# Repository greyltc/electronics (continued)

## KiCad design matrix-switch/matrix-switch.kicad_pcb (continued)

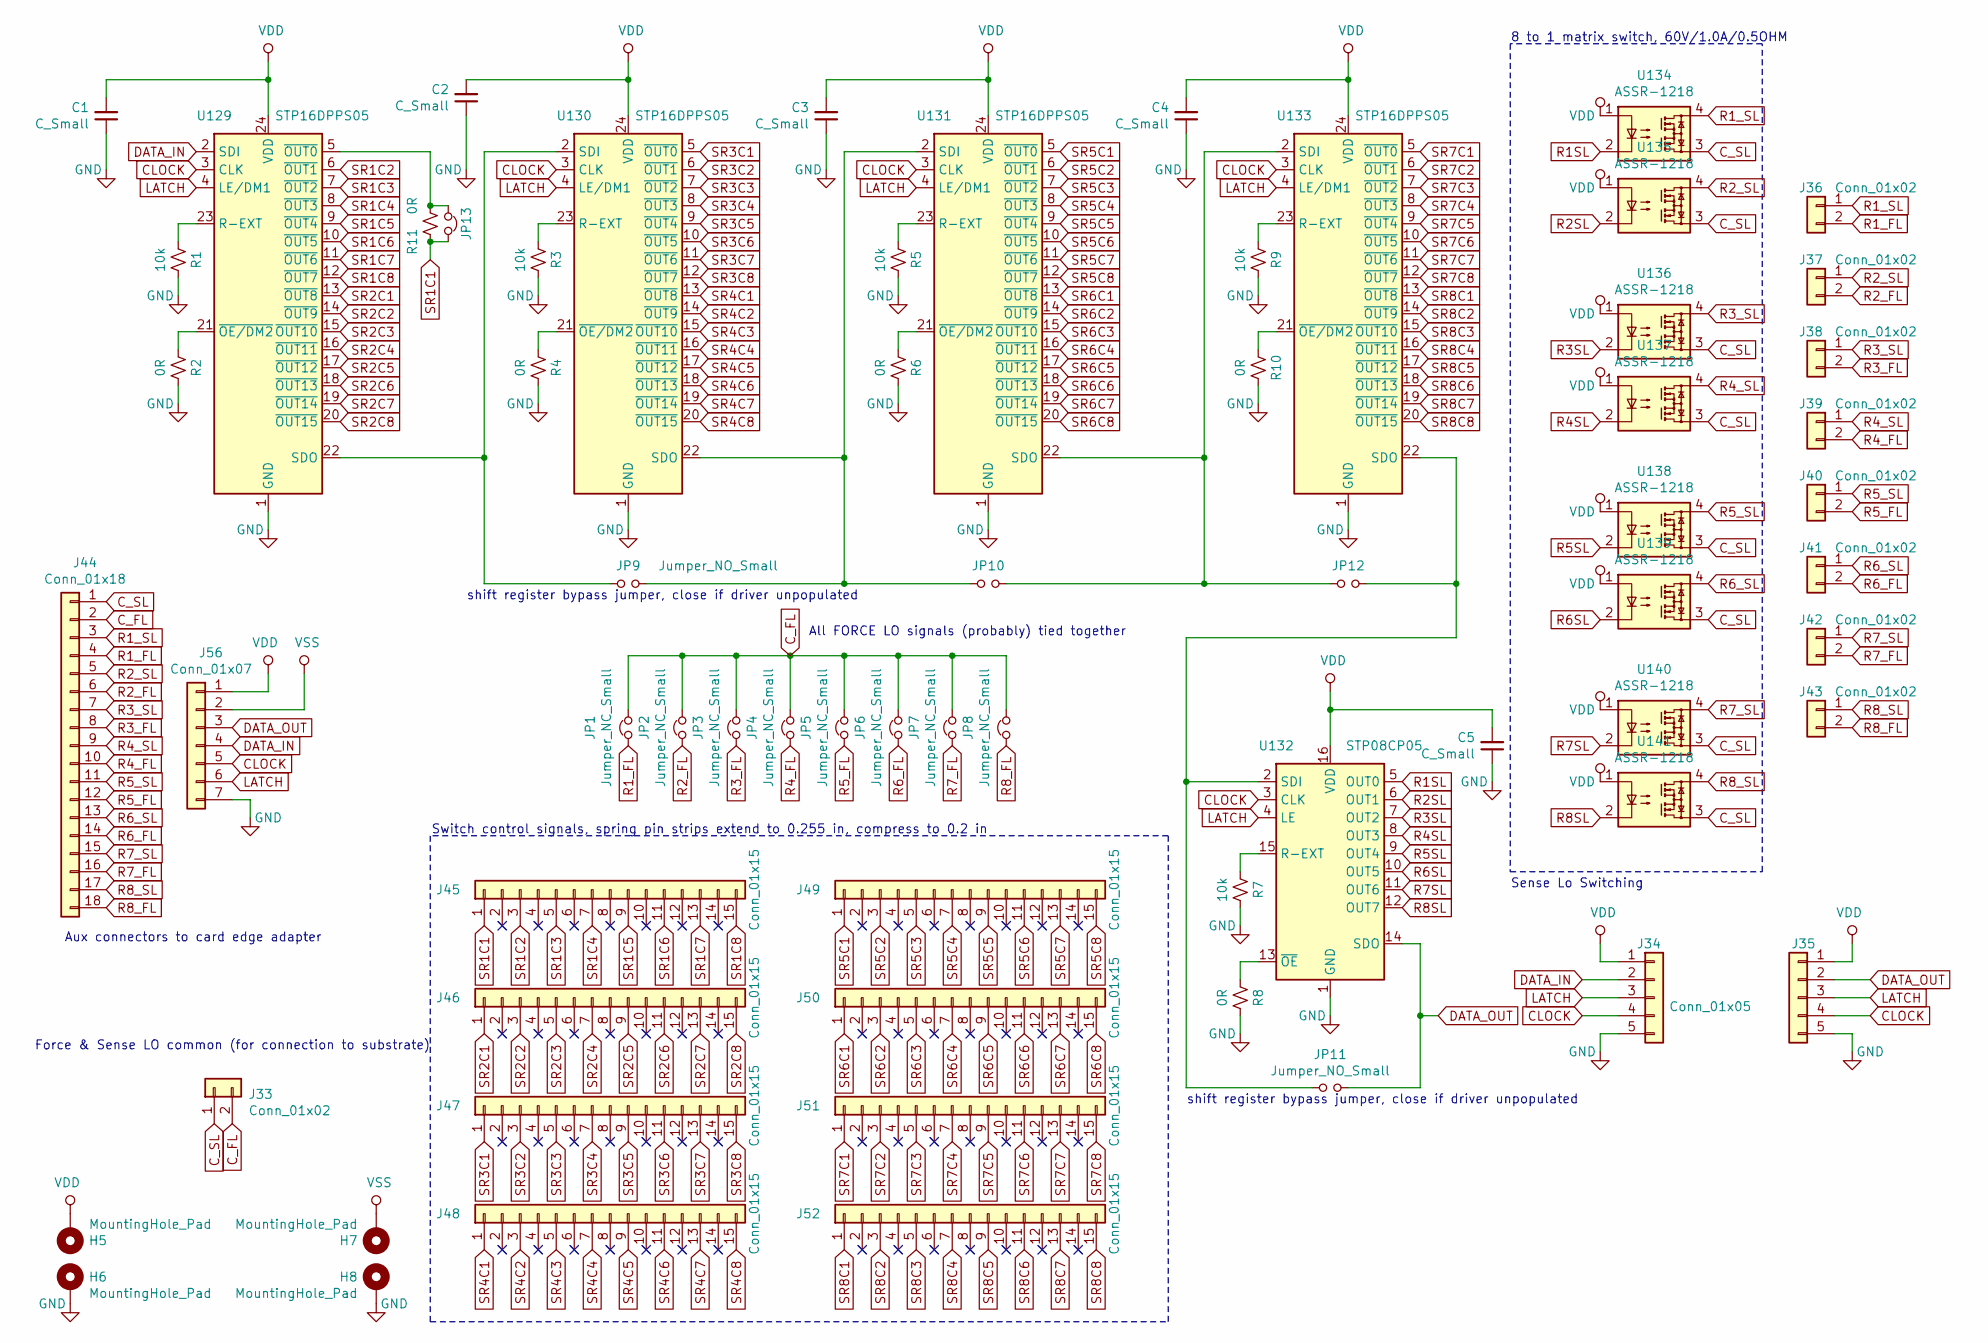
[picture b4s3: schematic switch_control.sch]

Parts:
C1, C2, C3, C4, C5: C_Small; C_0805_2012Metric
H5, H6, H7, H8: MountingHole_Pad; MountingHole_2.2mm_M2_Pad_Via
J33, J36, J37, J38, J39, J40, J41, J42, J43: Conn_01x02; PinHeader_1x02_P2.54mm_Vertical
J34, J35: Conn_01x05; PinHeader_1x05_P2.54mm_Vertical
J44: Conn_01x18; PinHeader_1x18_P2.54mm_Vertical
J45, J46, J47, J48, J49, J50, J51, J52: Conn_01x15; PinHeader_1x15_P2.54mm_Vertical; mfg_part 812-22-064-30-000101 millmax
J56: Conn_01x07; PinHeader_1x07_P2.54mm_Vertical
JP1, JP2, JP3, JP4, JP5, JP6, JP7, JP8, JP13: Jumper_NC_Small; SolderJumper-2_P1.3mm_Bridged_RoundedPad1.0x1.5mm
JP9, JP10, JP11, JP12: Jumper_NO_Small; SolderJumper-2_P1.3mm_Open_RoundedPad1.0x1.5mm
R1, R3, R5, R7, R9: 10k; R_0805_2012Metric
R2, R4, R6, R8, R10, R11: 0R; R_0805_2012Metric
U129, U130, U131, U133: STP16DPPS05; SOIC-24W_7.5x15.4mm_P1.27mm
U132: STP08CP05; SOIC-16_3.9x9.9mm_P1.27mm
U134, U135, U136, U137, U138, U139, U140, U141: ASSR-1218; SO-4_4.4x4.3mm_P2.54mm

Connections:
CLOCK: J34.4, J35.4, J56.5, U129.3 (CLK), U130.3 (CLK), U131.3 (CLK), U132.3 (CLK), U133.3 (CLK); also elsewhere on the board
C_FL: J33.2, J44.2, JP1.2, JP2.2, JP3.2, JP4.2, JP5.2, JP6.2, JP7.2, JP8.2; also elsewhere on the board
C_SL: J33.1, J44.1, U134.3, U135.3, U136.3, U137.3, U138.3, U139.3, U140.3, U141.3; also elsewhere on the board
DATA_IN: J34.2, J56.4, U129.2 (SDI); also elsewhere on the board
DATA_OUT: J35.2, J56.3, JP11.2, U132.14 (SDO); also elsewhere on the board
GND: C1.1, C2.1, C3.1, C4.1, C5.1, H6.1, H8.1, J34.5, J35.5, J56.7, R1.1, R2.1, R3.1, R4.1, R5.1, R6.1, R7.1, R8.1, R9.1, R10.1, U129.1 (GND), U130.1 (GND), U131.1 (GND), U132.1 (GND), U133.1 (GND); also elsewhere on the board
LATCH: J34.3, J35.3, J56.6, U129.4 (LE/DM1), U130.4 (LE/DM1), U131.4 (LE/DM1), U132.4 (LE), U133.4 (LE/DM1); also elsewhere on the board
unnamed: JP9.1, U129.22 (SDO), U130.2 (SDI)
unnamed: JP9.2, JP10.1, U130.22 (SDO), U131.2 (SDI)
unnamed: JP10.2, JP12.1, U131.22 (SDO), U133.2 (SDI)
unnamed: JP11.1, JP12.2, U132.2 (SDI), U133.22 (SDO)
unnamed: JP13.1, R11.1, U129.5 (~OUT0)
unnamed: R1.2, U129.23 (R-EXT)
unnamed: R2.2, U129.21 (~OE/DM2)
unnamed: R3.2, U130.23 (R-EXT)
unnamed: R4.2, U130.21 (~OE/DM2)
unnamed: R5.2, U131.23 (R-EXT)
unnamed: R6.2, U131.21 (~OE/DM2)
unnamed: R7.2, U132.15 (R-EXT)
unnamed: R8.2, U132.13 (~OE)
unnamed: R9.2, U133.23 (R-EXT)
unnamed: R10.2, U133.21 (~OE/DM2)
R1SL: U132.5 (OUT0), U134.2
R1_FL: J36.2, J44.4, JP1.1; also elsewhere on the board
R1_SL: J36.1, J44.3, U134.4; also elsewhere on the board
R2SL: U132.6 (OUT1), U135.2
R2_FL: J37.2, J44.6, JP2.1; also elsewhere on the board
R2_SL: J37.1, J44.5, U135.4; also elsewhere on the board
R3SL: U132.7 (OUT2), U136.2
R3_FL: J38.2, J44.8, JP3.1; also elsewhere on the board
R3_SL: J38.1, J44.7, U136.4; also elsewhere on the board
R4SL: U132.8 (OUT3), U137.2
R4_FL: J39.2, J44.10, JP4.1; also elsewhere on the board
R4_SL: J39.1, J44.9, U137.4; also elsewhere on the board
R5SL: U132.9 (OUT4), U138.2
R5_FL: J40.2, J44.12, JP5.1; also elsewhere on the board
R5_SL: J40.1, J44.11, U138.4; also elsewhere on the board
R6SL: U132.10 (OUT5), U139.2
R6_FL: J41.2, J44.14, JP6.1; also elsewhere on the board
R6_SL: J41.1, J44.13, U139.4; also elsewhere on the board
R7SL: U132.11 (OUT6), U140.2
R7_FL: J42.2, J44.16, JP7.1; also elsewhere on the board
R7_SL: J42.1, J44.15, U140.4; also elsewhere on the board
R8SL: U132.12 (OUT7), U141.2
R8_FL: J43.2, J44.18, JP8.1; also elsewhere on the board
R8_SL: J43.1, J44.17, U141.4; also elsewhere on the board
SR1C1: J45.1, JP13.2, R11.2
SR1C2: J45.3, U129.6 (~OUT1)
SR1C3: J45.5, U129.7 (~OUT2)
SR1C4: J45.7, U129.8 (~OUT3)
SR1C5: J45.9, U129.9 (~OUT4)
SR1C6: J45.11, U129.10 (~OUT5)
SR1C7: J45.13, U129.11 (~OUT6)
SR1C8: J45.15, U129.12 (~OUT7)
SR2C1: J46.1, U129.13 (~OUT8)
SR2C2: J46.3, U129.14 (~OUT9)
SR2C3: J46.5, U129.15 (~OUT10)
SR2C4: J46.7, U129.16 (~OUT11)
SR2C5: J46.9, U129.17 (~OUT12)
SR2C6: J46.11, U129.18 (~OUT13)
SR2C7: J46.13, U129.19 (~OUT14)
SR2C8: J46.15, U129.20 (~OUT15)
SR3C1: J47.1, U130.5 (~OUT0)
SR3C2: J47.3, U130.6 (~OUT1)
SR3C3: J47.5, U130.7 (~OUT2)
SR3C4: J47.7, U130.8 (~OUT3)
SR3C5: J47.9, U130.9 (~OUT4)
SR3C6: J47.11, U130.10 (~OUT5)
SR3C7: J47.13, U130.11 (~OUT6)
SR3C8: J47.15, U130.12 (~OUT7)
SR4C1: J48.1, U130.13 (~OUT8)
SR4C2: J48.3, U130.14 (~OUT9)
SR4C3: J48.5, U130.15 (~OUT10)
SR4C4: J48.7, U130.16 (~OUT11)
SR4C5: J48.9, U130.17 (~OUT12)
SR4C6: J48.11, U130.18 (~OUT13)
SR4C7: J48.13, U130.19 (~OUT14)
SR4C8: J48.15, U130.20 (~OUT15)
SR5C1: J49.1, U131.5 (~OUT0)
SR5C2: J49.3, U131.6 (~OUT1)
SR5C3: J49.5, U131.7 (~OUT2)
SR5C4: J49.7, U131.8 (~OUT3)
SR5C5: J49.9, U131.9 (~OUT4)
SR5C6: J49.11, U131.10 (~OUT5)
SR5C7: J49.13, U131.11 (~OUT6)
SR5C8: J49.15, U131.12 (~OUT7)
SR6C1: J50.1, U131.13 (~OUT8)
SR6C2: J50.3, U131.14 (~OUT9)
SR6C3: J50.5, U131.15 (~OUT10)
SR6C4: J50.7, U131.16 (~OUT11)
SR6C5: J50.9, U131.17 (~OUT12)
SR6C6: J50.11, U131.18 (~OUT13)
SR6C7: J50.13, U131.19 (~OUT14)
SR6C8: J50.15, U131.20 (~OUT15)
SR7C1: J51.1, U133.5 (~OUT0)
SR7C2: J51.3, U133.6 (~OUT1)
SR7C3: J51.5, U133.7 (~OUT2)
SR7C4: J51.7, U133.8 (~OUT3)
SR7C5: J51.9, U133.9 (~OUT4)
SR7C6: J51.11, U133.10 (~OUT5)
SR7C7: J51.13, U133.11 (~OUT6)
SR7C8: J51.15, U133.12 (~OUT7)
SR8C1: J52.1, U133.13 (~OUT8)
SR8C2: J52.3, U133.14 (~OUT9)
SR8C3: J52.5, U133.15 (~OUT10)
SR8C4: J52.7, U133.16 (~OUT11)
SR8C5: J52.9, U133.17 (~OUT12)
SR8C6: J52.11, U133.18 (~OUT13)
SR8C7: J52.13, U133.19 (~OUT14)
SR8C8: J52.15, U133.20 (~OUT15)
VDD: C1.2, C2.2, C3.2, C4.2, C5.2, H5.1, J34.1, J35.1, J56.1, U129.24 (VDD), U130.24 (VDD), U131.24 (VDD), U132.16 (VDD), U133.24 (VDD), U134.1, U135.1, U136.1, U137.1, U138.1, U139.1, U140.1, U141.1; also elsewhere on the board
VSS: H7.1, J56.2; also elsewhere on the board

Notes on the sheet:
8 to 1 matrix switch, 60V/1.0A/0.5OHM
All FORCE LO signals (probably) tied together
Sense Lo Switching
Force & Sense LO common (for connection to substrate)
shift register bypass jumper, close if driver unpopulated
Aux connectors to card edge adapter
Switch control signals, spring pin strips extend to 0.255 in, compress to 0.2 in

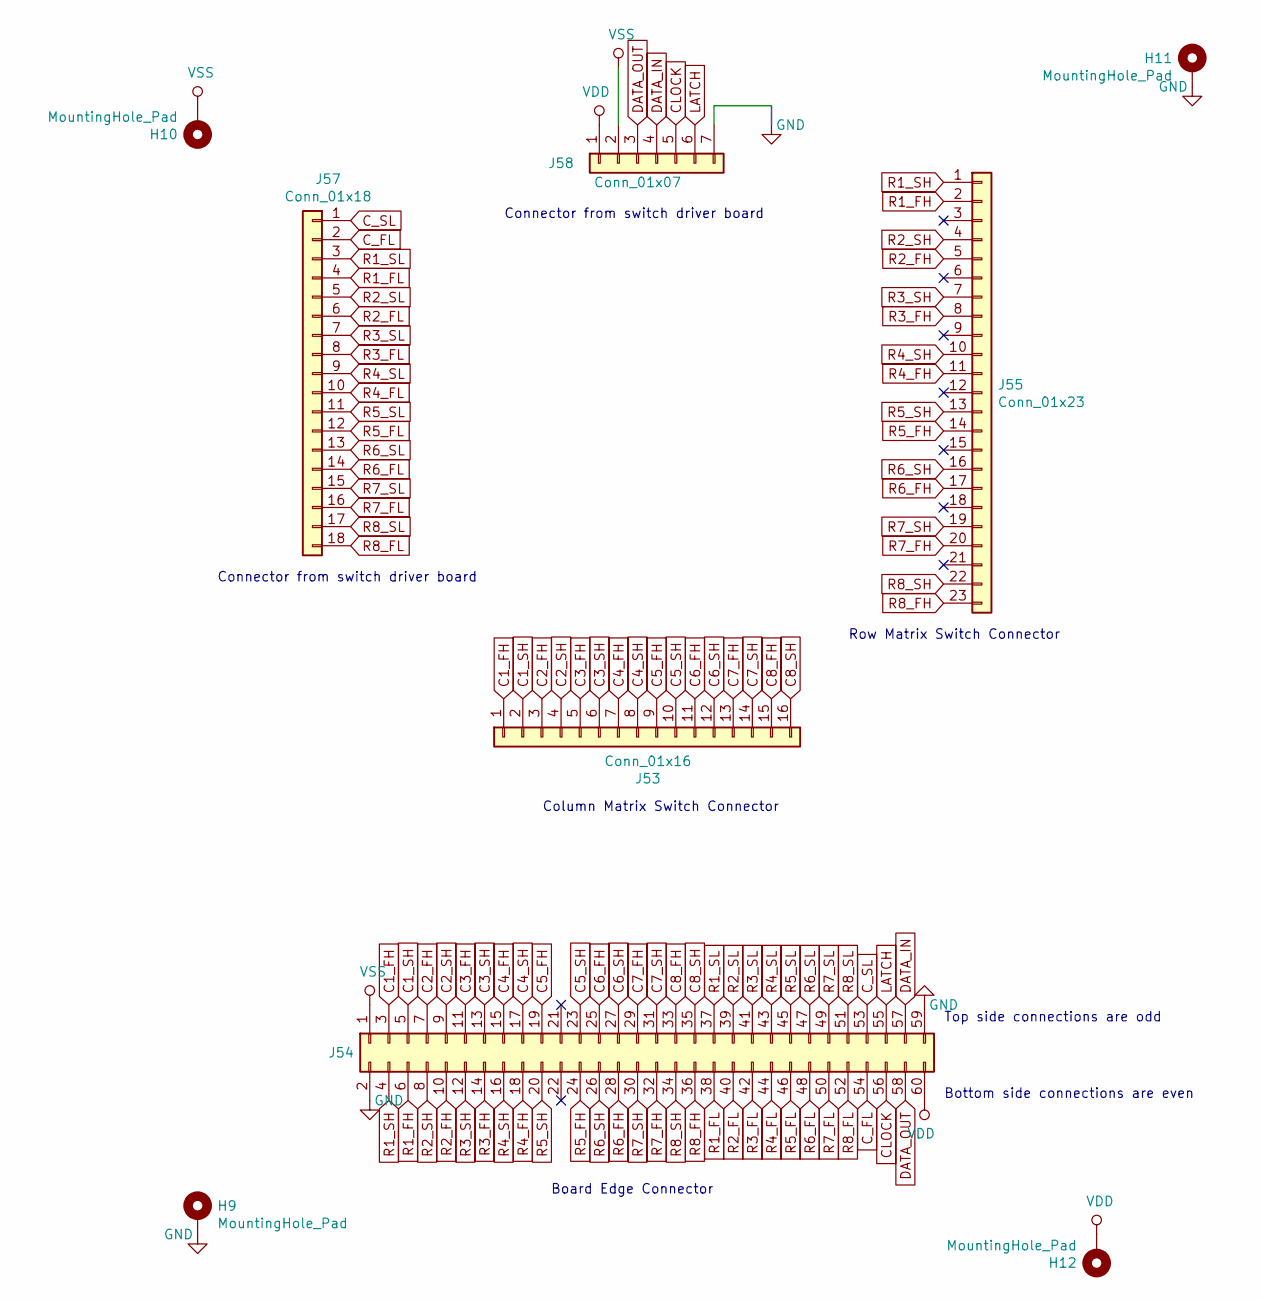
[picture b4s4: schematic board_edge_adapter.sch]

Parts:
H9, H10, H11, H12: MountingHole_Pad; MountingHole_2.2mm_M2_Pad_Via
J53: Conn_01x16; PinHeader_1x16_P2.54mm_Vertical
J54: Conn_02x30_Odd_Even; Samtec_MECF-30-0_-L-DV_2x30_P1.27mm_Polarized_Edge
J55: Conn_01x23; PinHeader_1x23_P2.54mm_Vertical
J57: Conn_01x18; PinHeader_1x18_P2.54mm_Horizontal
J58: Conn_01x07; PinHeader_1x07_P2.54mm_Horizontal

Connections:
C1_FH: J53.1, J54.3; also elsewhere on the board
C1_SH: J53.2, J54.5; also elsewhere on the board
C2_FH: J53.3, J54.7; also elsewhere on the board
C2_SH: J53.4, J54.9; also elsewhere on the board
C3_FH: J53.5, J54.11; also elsewhere on the board
C3_SH: J53.6, J54.13; also elsewhere on the board
C4_FH: J53.7, J54.15; also elsewhere on the board
C4_SH: J53.8, J54.17; also elsewhere on the board
C5_FH: J53.9, J54.19; also elsewhere on the board
C5_SH: J53.10, J54.23; also elsewhere on the board
C6_FH: J53.11, J54.25; also elsewhere on the board
C6_SH: J53.12, J54.27; also elsewhere on the board
C7_FH: J53.13, J54.29; also elsewhere on the board
C7_SH: J53.14, J54.31; also elsewhere on the board
C8_FH: J53.15, J54.33; also elsewhere on the board
C8_SH: J53.16, J54.35; also elsewhere on the board
CLOCK: J54.56, J58.5; also elsewhere on the board
C_FL: J54.54, J57.2; also elsewhere on the board
C_SL: J54.53, J57.1; also elsewhere on the board
DATA_IN: J54.57, J58.4; also elsewhere on the board
DATA_OUT: J54.58, J58.3; also elsewhere on the board
GND: H9.1, H11.1, J54.2, J54.59, J58.7; also elsewhere on the board
LATCH: J54.55, J58.6; also elsewhere on the board
R1_FH: J54.6, J55.2; also elsewhere on the board
R1_FL: J54.38, J57.4; also elsewhere on the board
R1_SH: J54.4, J55.1; also elsewhere on the board
R1_SL: J54.37, J57.3; also elsewhere on the board
R2_FH: J54.10, J55.5; also elsewhere on the board
R2_FL: J54.40, J57.6; also elsewhere on the board
R2_SH: J54.8, J55.4; also elsewhere on the board
R2_SL: J54.39, J57.5; also elsewhere on the board
R3_FH: J54.14, J55.8; also elsewhere on the board
R3_FL: J54.42, J57.8; also elsewhere on the board
R3_SH: J54.12, J55.7; also elsewhere on the board
R3_SL: J54.41, J57.7; also elsewhere on the board
R4_FH: J54.18, J55.11; also elsewhere on the board
R4_FL: J54.44, J57.10; also elsewhere on the board
R4_SH: J54.16, J55.10; also elsewhere on the board
R4_SL: J54.43, J57.9; also elsewhere on the board
R5_FH: J54.24, J55.14; also elsewhere on the board
R5_FL: J54.46, J57.12; also elsewhere on the board
R5_SH: J54.20, J55.13; also elsewhere on the board
R5_SL: J54.45, J57.11; also elsewhere on the board
R6_FH: J54.28, J55.17; also elsewhere on the board
R6_FL: J54.48, J57.14; also elsewhere on the board
R6_SH: J54.26, J55.16; also elsewhere on the board
R6_SL: J54.47, J57.13; also elsewhere on the board
R7_FH: J54.32, J55.20; also elsewhere on the board
R7_FL: J54.50, J57.16; also elsewhere on the board
R7_SH: J54.30, J55.19; also elsewhere on the board
R7_SL: J54.49, J57.15; also elsewhere on the board
R8_FH: J54.36, J55.23; also elsewhere on the board
R8_FL: J54.52, J57.18; also elsewhere on the board
R8_SH: J54.34, J55.22; also elsewhere on the board
R8_SL: J54.51, J57.17; also elsewhere on the board
VDD: H12.1, J54.60, J58.1; also elsewhere on the board
VSS: H10.1, J54.1, J58.2; also elsewhere on the board

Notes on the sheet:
Column Matrix Switch Connector
Top side connections are odd
Bottom side connections are even
Board Edge Connector
Connector from switch driver board
Row Matrix Switch Connector

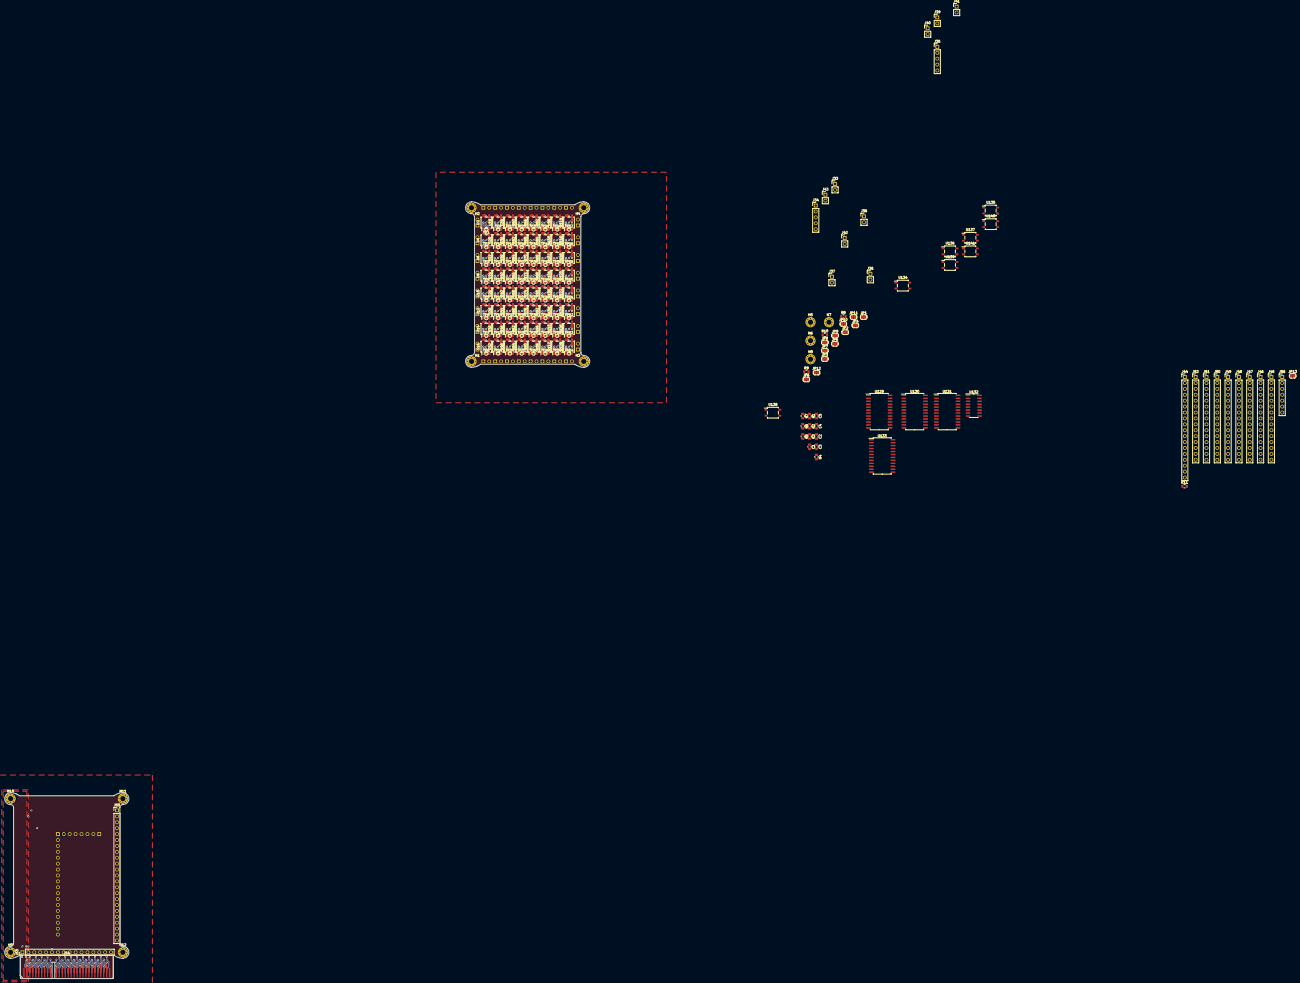
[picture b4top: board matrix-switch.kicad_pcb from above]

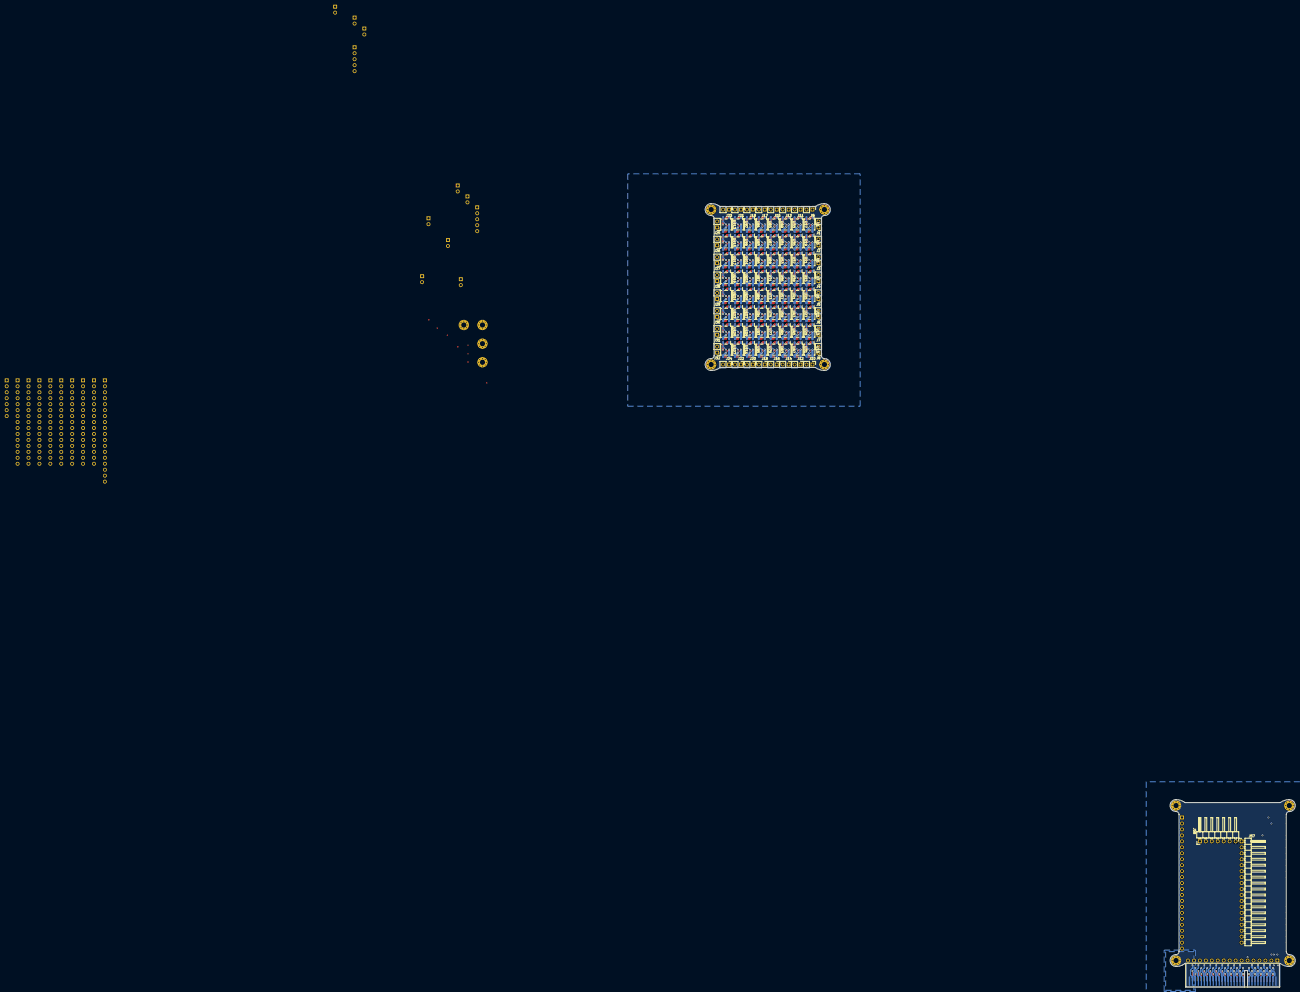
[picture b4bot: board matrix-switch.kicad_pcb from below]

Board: 4 copper layers, 304 parts (98 on the bottom side), 272 nets.

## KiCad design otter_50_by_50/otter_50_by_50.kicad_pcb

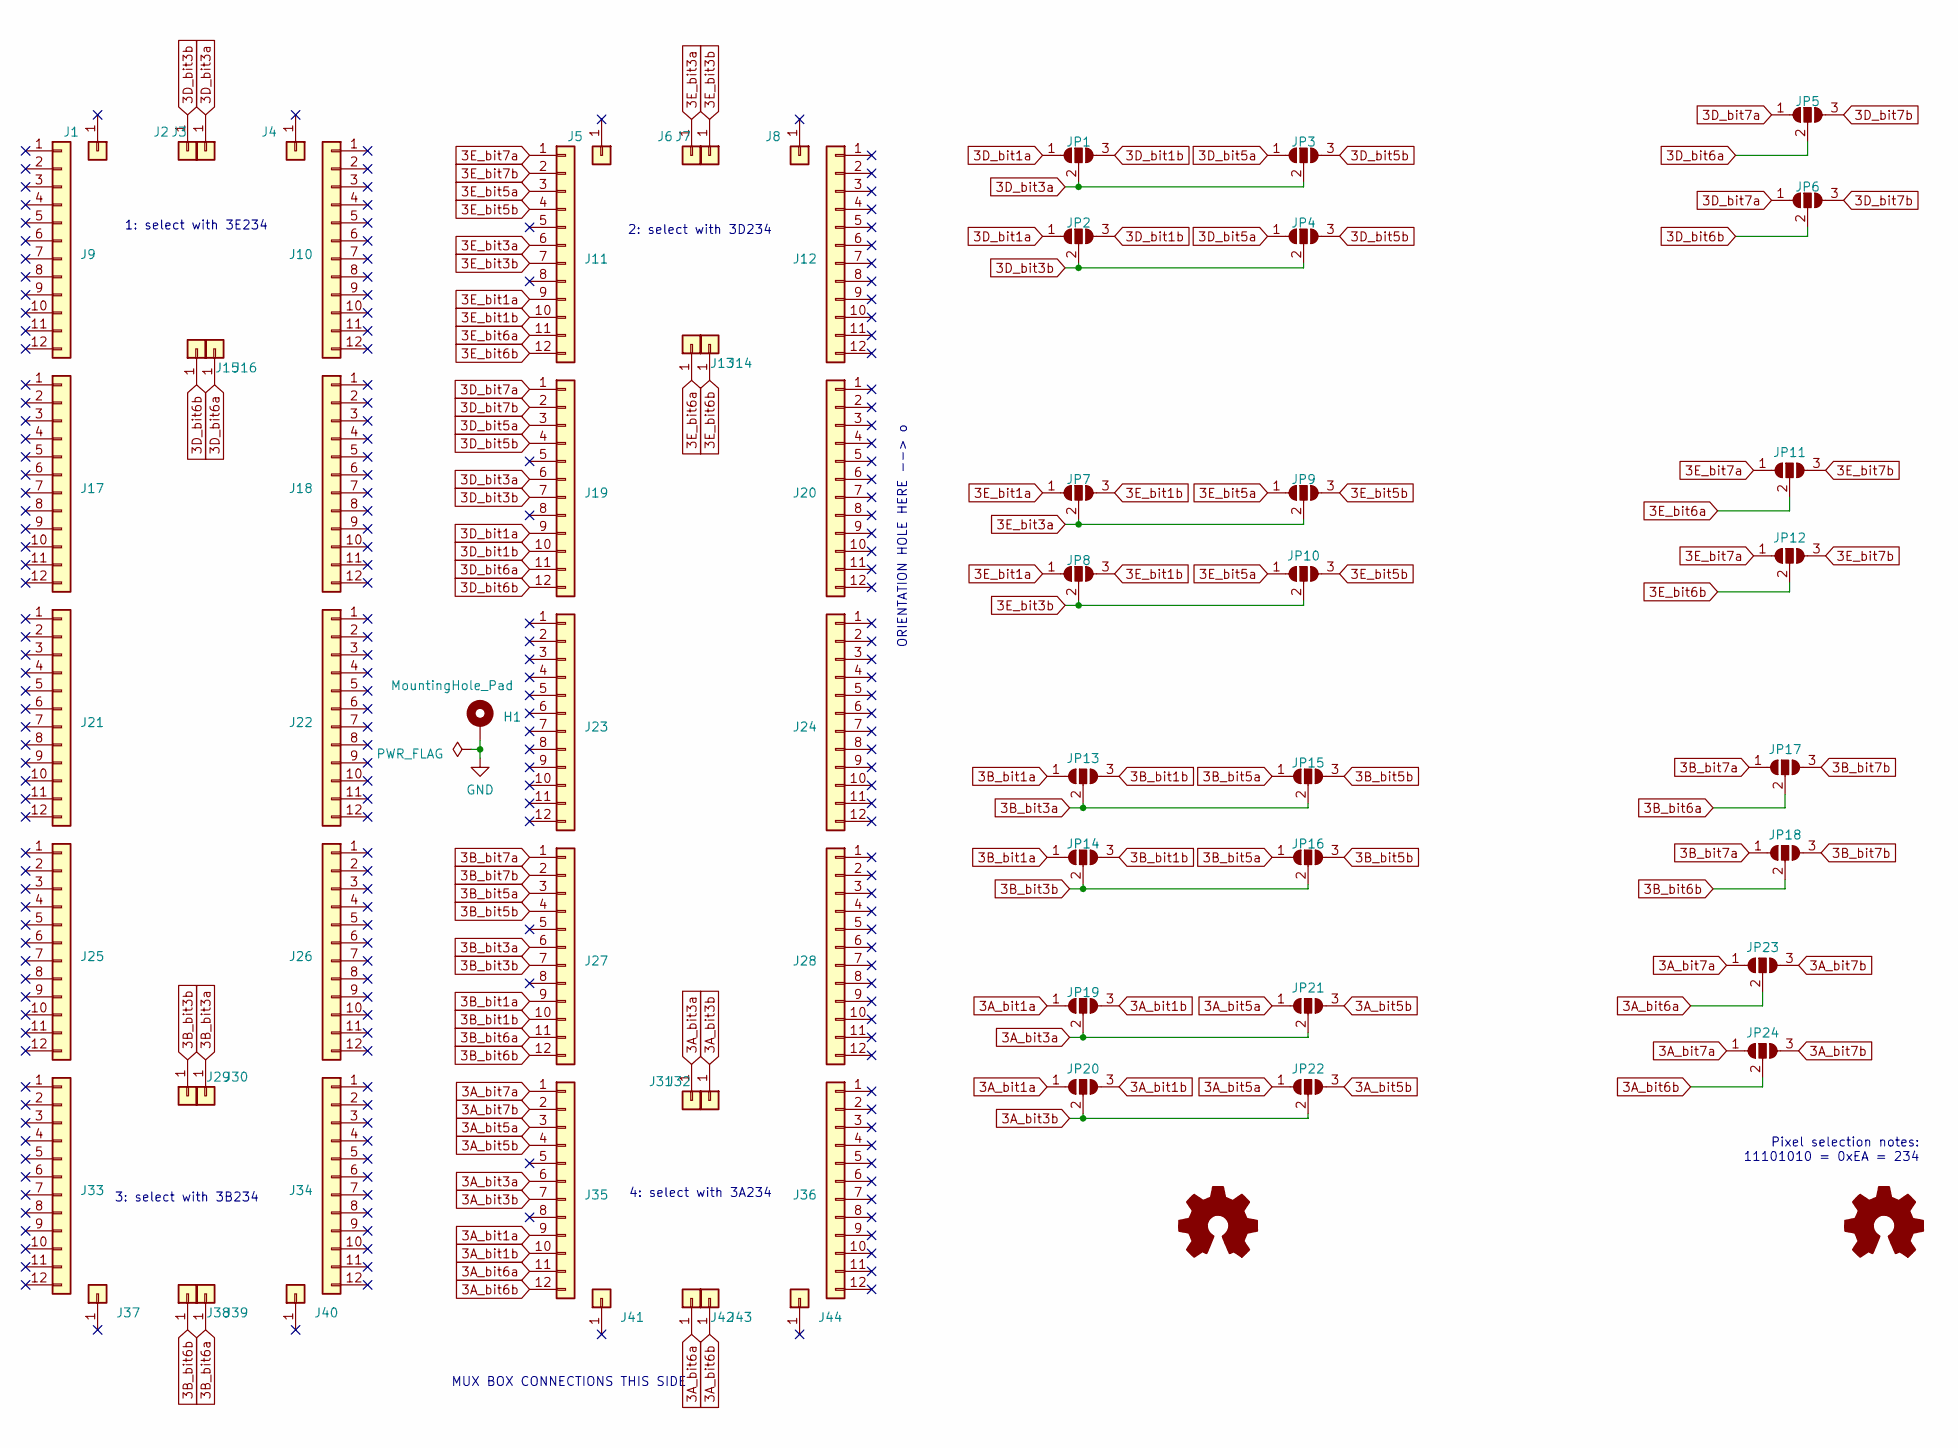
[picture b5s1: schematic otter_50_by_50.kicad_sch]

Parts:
H1: MountingHole_Pad; MountingHole_2.2mm_M2_Pad_Via
J1, J2, J3, J4, J5, J6, J7, J8, J13, J14, J15, J16, J29, J30, J31, J32, J37, J38, J39, J40, J41, J42, J43, J44: Conn_01x01; spring_pin
J9, J10, J11, J12, J17, J18, J19, J20, J21, J22, J23, J24, J25, J26, J27, J28, J33, J34, J35, J36: Conn_01x12; PinHeader_1x12_P2.00mm_Vertical
JP1, JP2, JP3, JP4, JP5, JP6, JP7, JP8, JP9, JP10, JP11, JP12, JP13, JP14, JP15, JP16, JP17, JP18, JP19, JP20, JP21, JP22, JP23, JP24: SolderJumper_3_Open; SolderJumper-3_P2.0mm_Open_TrianglePad1.0x1.5mm_NumberLabels
LOGO1, LOGO2: Logo_Open_Hardware_Small; site_small

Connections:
3A_bit1a: J35.9, JP19.1 (A), JP20.1 (A)
3A_bit1b: J35.10, JP19.3 (B), JP20.3 (B)
3A_bit3a: J31.1, J35.6, JP19.2 (C), JP21.2 (C)
3A_bit3b: J32.1, J35.7, JP20.2 (C), JP22.2 (C)
3A_bit5a: J35.3, JP21.1 (A), JP22.1 (A)
3A_bit5b: J35.4, JP21.3 (B), JP22.3 (B)
3A_bit6a: J35.11, J42.1, JP23.2 (C)
3A_bit6b: J35.12, J43.1, JP24.2 (C)
3A_bit7a: J35.1, JP23.1 (A), JP24.1 (A)
3A_bit7b: J35.2, JP23.3 (B), JP24.3 (B)
3B_bit1a: J27.9, JP13.1 (A), JP14.1 (A)
3B_bit1b: J27.10, JP13.3 (B), JP14.3 (B)
3B_bit3a: J27.6, J30.1, JP13.2 (C), JP15.2 (C)
3B_bit3b: J27.7, J29.1, JP14.2 (C), JP16.2 (C)
3B_bit5a: J27.3, JP15.1 (A), JP16.1 (A)
3B_bit5b: J27.4, JP15.3 (B), JP16.3 (B)
3B_bit6a: J27.11, J39.1, JP17.2 (C)
3B_bit6b: J27.12, J38.1, JP18.2 (C)
3B_bit7a: J27.1, JP17.1 (A), JP18.1 (A)
3B_bit7b: J27.2, JP17.3 (B), JP18.3 (B)
3D_bit1a: J19.9, JP1.1 (A), JP2.1 (A)
3D_bit1b: J19.10, JP1.3 (B), JP2.3 (B)
3D_bit3a: J3.1, J19.6, JP1.2 (C), JP3.2 (C)
3D_bit3b: J2.1, J19.7, JP2.2 (C), JP4.2 (C)
3D_bit5a: J19.3, JP3.1 (A), JP4.1 (A)
3D_bit5b: J19.4, JP3.3 (B), JP4.3 (B)
3D_bit6a: J16.1, J19.11, JP5.2 (C)
3D_bit6b: J15.1, J19.12, JP6.2 (C)
3D_bit7a: J19.1, JP5.1 (A), JP6.1 (A)
3D_bit7b: J19.2, JP5.3 (B), JP6.3 (B)
3E_bit1a: J11.9, JP7.1 (A), JP8.1 (A)
3E_bit1b: J11.10, JP7.3 (B), JP8.3 (B)
3E_bit3a: J6.1, J11.6, JP7.2 (C), JP9.2 (C)
3E_bit3b: J7.1, J11.7, JP8.2 (C), JP10.2 (C)
3E_bit5a: J11.3, JP9.1 (A), JP10.1 (A)
3E_bit5b: J11.4, JP9.3 (B), JP10.3 (B)
3E_bit6a: J11.11, J13.1, JP11.2 (C)
3E_bit6b: J11.12, J14.1, JP12.2 (C)
3E_bit7a: J11.1, JP11.1 (A), JP12.1 (A)
3E_bit7b: J11.2, JP11.3 (B), JP12.3 (B)
GND: H1.1

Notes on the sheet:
3: select with 3B234
1: select with 3E234
MUX BOX CONNECTIONS THIS SIDE
2: select with 3D234
4: select with 3A234
ORIENTATION HOLE HERE --> o
Pixel selection notes: 11101010 = 0xEA = 234

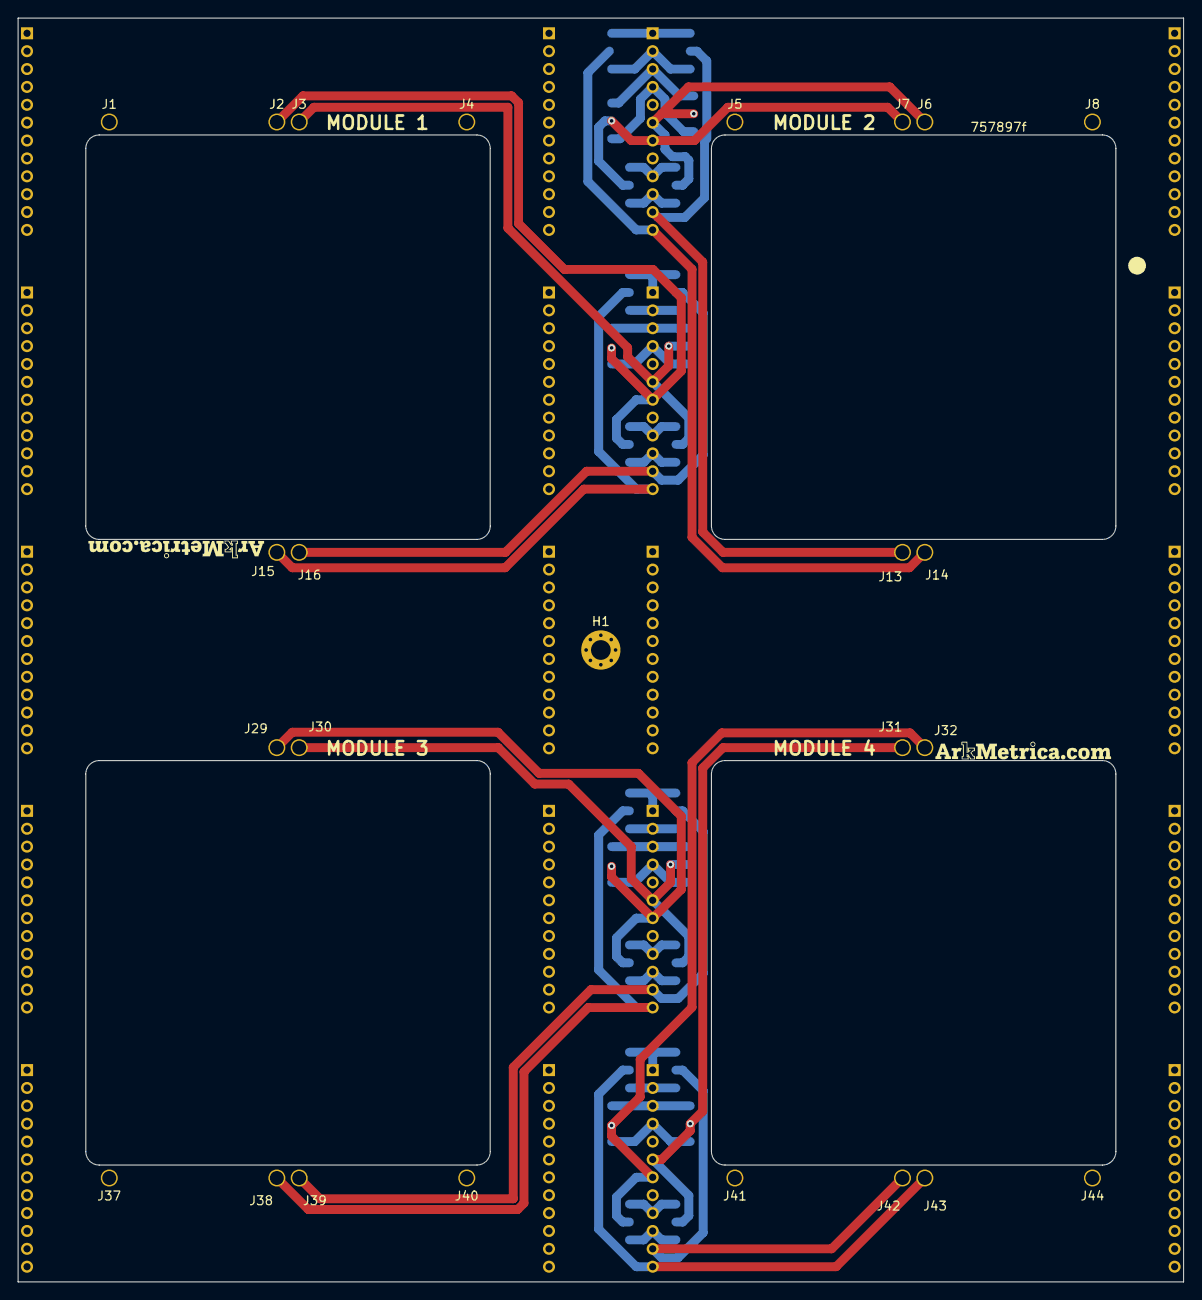
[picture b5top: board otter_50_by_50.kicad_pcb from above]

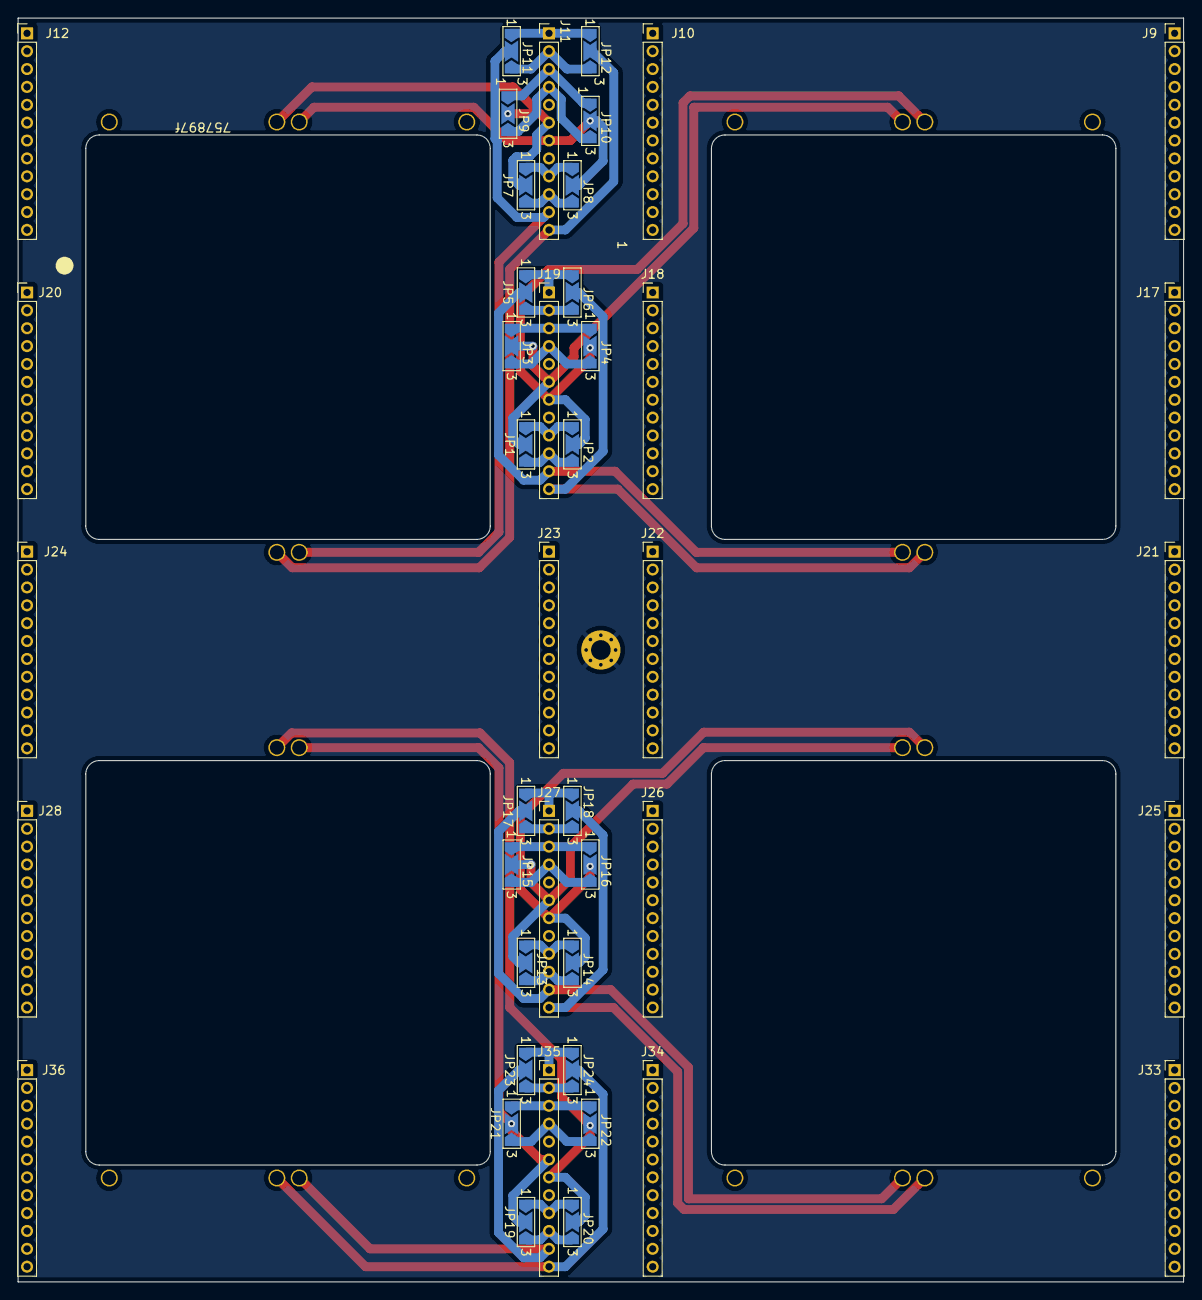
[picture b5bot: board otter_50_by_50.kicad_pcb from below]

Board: 2 copper layers, 130.4 x 141.4 mm, 71 parts (44 on the bottom side), 40 nets.
